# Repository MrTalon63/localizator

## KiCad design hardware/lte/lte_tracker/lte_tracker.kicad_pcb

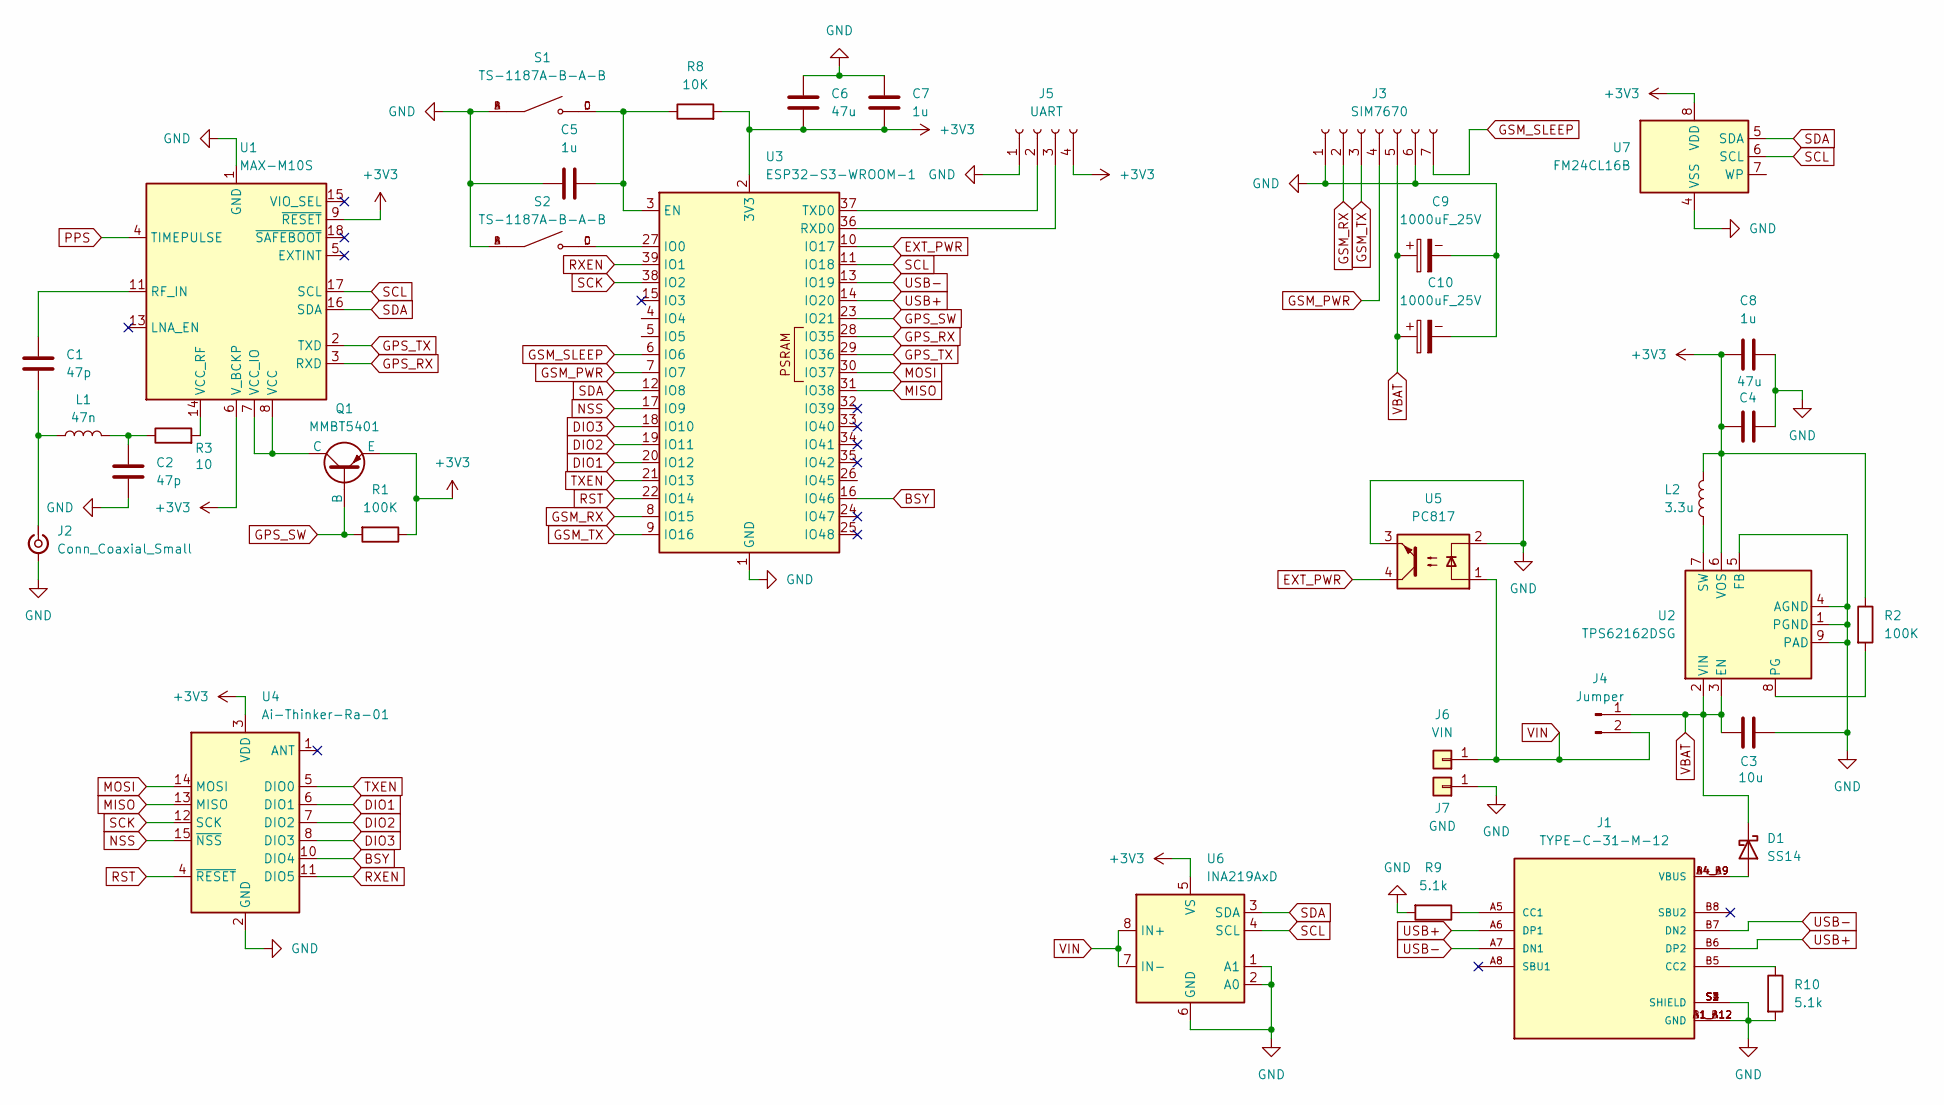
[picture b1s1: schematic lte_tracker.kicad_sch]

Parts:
C1, C2: 47p; C_0603_1608Metric
C3: 10u; C_1206_3216Metric
C4, C6: 47u; C_1206_3216Metric
C5, C7, C8: 1u; C_0805_2012Metric
C9, C10: 1000uF_25V; CP_Radial_D8.0mm_P2.50mm
D1: SS14; D_SMA
J1: TYPE-C-31-M-12; HRO_TYPE-C-31-M-12; PARTREV 2020.12.08
J2: Conn_Coaxial_Small; U.FL_Molex_MCRF_73412-0110_Vertical
J3: SIM7670; PinHeader_1x07_P2.54mm_Vertical
J4: Jumper; PinHeader_1x02_P2.54mm_Vertical
J5: UART; PinHeader_1x04_P2.54mm_Vertical
J6: VIN; TestPoint_Pad_2.5x2.5mm
J7: GND; TestPoint_Pad_2.5x2.5mm
L1: 47n; L_0603_1608Metric
L2: 3.3u; L_Vishay_IHLP-2525
Q1: MMBT5401; SOT-23
R1, R2: 100K; R_0603_1608Metric
R3: 10; R_0805_2012Metric
R8: 10K; R_0603_1608Metric
R9, R10: 5.1k; R_0402_1005Metric
S1, S2: TS-1187A-B-A-B; SW_TS-1187A-B-A-B; PARTREV A0
U1: MAX-M10S; ublox_MAX
U2: TPS62162DSG; WSON-8-1EP_2x2mm_P0.5mm_EP0.9x1.6mm_ThermalVias
U3: ESP32-S3-WROOM-1
U4: Ai-Thinker-Ra-01; Ai-Thinker-Ra-01-LoRa
U5: PC817; DIP-4_W7.62mm
U6: INA219AxD; SOIC-8_3.9x4.9mm_P1.27mm
U7: FM24CL16B; SOIC-8_3.9x4.9mm_P1.27mm

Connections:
+3V3: C4.1, C6.2, C7.2, C8.2, J5.4, L2.2, Q1.3 (E), R1.1, R2.1, R8.2, U1.6 (V_BCKP), U1.9 (~RESET), U2.6 (VOS), U3.2 (3V3), U4.3 (VDD), U6.5 (VS), U7.8 (VDD)
BSY: U3.16 (IO46), U4.10 (DIO4)
DIO1: U3.20 (IO12), U4.6 (DIO1)
DIO2: U3.19 (IO11), U4.7 (DIO2)
DIO3: U3.18 (IO10), U4.8 (DIO3)
EXT_PWR: U3.10 (IO17), U5.4
GND: C2.2, C3.1, C4.2, C5.2, C6.1, C7.1, C8.1, C9.2, C10.2, J1.A1_B12 (GND), J1.B1_A12 (GND), J1.S1 (SHIELD), J1.S2 (SHIELD), J1.S3 (SHIELD), J1.S4 (SHIELD), J2.2 (Ext), J3.1, J3.6, J5.1, J7.1, R9.2, R10.2, S1.A, S1.B, S2.A, S2.B, U1.1 (GND), U1.10 (GND), U1.12 (GND), U2.1 (PGND), U2.4 (AGND), U2.5 (FB), U2.9 (PAD), U3.1 (GND), U3.40 (GND), U3.41 (GND), U4.2 (GND), U4.9 (GND), U4.16 (GND), U5.2, U5.3, U6.1 (A1), U6.2 (A0), U6.6 (GND), U7.4 (VSS)
GPS_RX: U1.3 (RXD), U3.28 (IO35)
GPS_SW: Q1.2 (B), R1.2, U3.23 (IO21)
GPS_TX: U1.2 (TXD), U3.29 (IO36)
GSM_PWR: J3.4, U3.7 (IO7)
GSM_RX: J3.2, U3.8 (IO15)
GSM_SLEEP: J3.7, U3.6 (IO6)
GSM_TX: J3.3, U3.9 (IO16)
MISO: U3.31 (IO38), U4.13 (MISO)
MOSI: U3.30 (IO37), U4.14 (MOSI)
NSS: U3.17 (IO9), U4.15 (~NSS)
unnamed: C2.1, L1.2, R3.1
unnamed: D1.2 (A), J1.A4_B9 (VBUS), J1.B4_A9 (VBUS)
unnamed: J1.A5 (CC1), R9.1
unnamed: J1.B5 (CC2), R10.1
unnamed: C1.2, J2.1 (In), L1.1
unnamed: J5.2, U3.37 (TXD0)
unnamed: J5.3, U3.36 (RXD0)
unnamed: Q1.1 (C), U1.7 (VCC_IO), U1.8 (VCC)
unnamed: C1.1, U1.11 (RF_IN)
unnamed: R3.2, U1.14 (VCC_RF)
unnamed: R2.2, U2.8 (PG)
unnamed: L2.1, U2.7 (SW)
unnamed: C5.1, R8.1, S1.C, S1.D, U3.3 (EN)
unnamed: S2.C, S2.D, U3.27 (IO0)
PPS: U1.4 (TIMEPULSE)
RST: U3.22 (IO14), U4.4 (~RESET)
RXEN: U3.39 (IO1), U4.11 (DIO5)
SCK: U3.38 (IO2), U4.12 (SCK)
SCL: U1.17 (SCL), U3.11 (IO18), U6.4 (SCL), U7.6 (SCL)
SDA: U1.16 (SDA), U3.12 (IO8), U6.3 (SDA), U7.5 (SDA)
TXEN: U3.21 (IO13), U4.5 (DIO0)
USB+: J1.A6 (DP1), J1.B6 (DP2), U3.14 (IO20)
USB-: J1.A7 (DN1), J1.B7 (DN2), U3.13 (IO19)
VBAT: C3.2, C9.1, C10.1, D1.1 (K), J3.5, J4.1, U2.2 (VIN), U2.3 (EN)
VIN: J4.2, J6.1, U5.1, U6.7 (IN-), U6.8 (IN+)

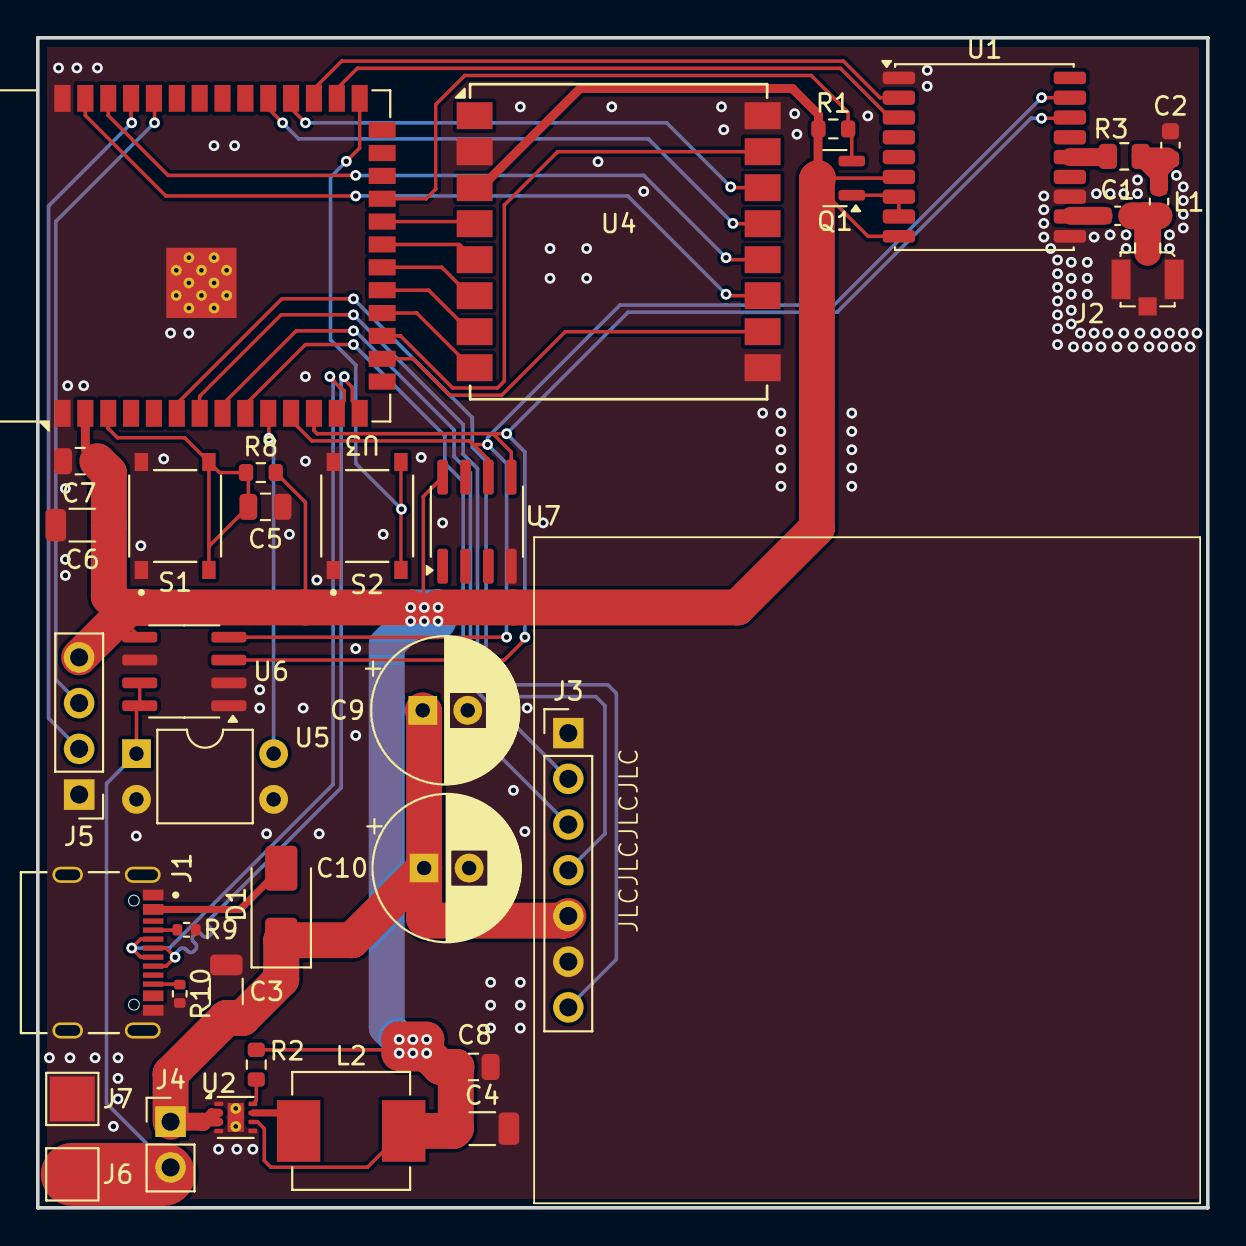
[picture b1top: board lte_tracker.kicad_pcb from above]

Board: 2 copper layers, 65.0 x 65.0 mm, 36 parts (0 on the bottom side), 41 nets.

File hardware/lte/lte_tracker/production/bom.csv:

Designator,Footprint,Quantity,Value,LCSC Part #
"C1, C2",0603,2,47p,
C3,1206,1,10u,
"C4, C6",1206,2,47u,
"C5, C7, C8",0805,3,1u,
D1,D_SMA,1,SS14,
J1,HRO_TYPE-C-31-M-12,1,TYPE-C-31-M-12,
J2,U.FL_Molex_MCRF_73412-0110_Vertical,1,Conn_Coaxial_Small,
J4,PinHeader_1x02_P2.54mm_Vertical,1,Jumper,
J5,PinHeader_1x04_P2.54mm_Vertical,1,UART,
J6,TestPoint_Pad_2.5x2.5mm,1,VIN,
J7,TestPoint_Pad_2.5x2.5mm,1,GND,
L1,0603,1,47n,
L2,L_Vishay_IHLP-2525,1,3.3u,
Q1,SOT-23,1,MMBT5401,
"R1, R2",0603,2,100K,
"R10, R9",0402,2,5.1k,
R3,0805,1,10,
R8,0603,1,10K,
"S1, S2",SW_TS-1187A-B-A-B,2,TS-1187A-B-A-B,
U1,ublox_MAX,1,MAX-M10S,
U2,WSON-8-1EP_2x2mm_P0.5mm_EP0.9x1.6mm_ThermalVias,1,TPS62162DSG,
U3,ESP32-S3-WROOM-1,1,ESP32-S3-WROOM-1,
U4,Ai-Thinker-Ra-01-LoRa,1,Ai-Thinker-Ra-01,

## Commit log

2024-04-22 POC Svelte frontend
2024-04-22 Clear whole localstorage
2024-04-22 Update login route
2024-04-22 Test an APRS icon
2024-04-22 Change date format and default icon
2024-04-22 Add time selector
2024-05-01 Add device type to the popup
2024-05-01 Change icon to car if device type is tracker
2024-05-02 Add meters to subpoints
2024-05-08 Add icons and beta colors
2024-10-25 LTE Hardware
